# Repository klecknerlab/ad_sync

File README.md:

# ad_sync
Hardware and software design for a USB-based analog/digital synchronizer board.  Developed by the MUVI and Kleckner Labs at UC Merced.

## Description
This project is intended to solve a specific problem: synchronizing a laser scanner and camera setup for 3D volumetric imaging.
To do this, it outputs hardware synchronized digital and analog signals.
The hardware works by converting a single digital bit stream from the on board ESP32 processor to a series of shift registers and a digital-to-analog converter (with ± 10V range).
The update rate is tunable from 30 Hz to 700 kHz, with a ~10 PPM accurate clock (provided by the APLL clock on the ESP32).

The hardware, firmware and software required to run the board is all stored in this repository, with an Apache license.
If you would like to fabricate, modify, or just use these boards, get in touch!

## Features
* 16 synchronized digital outputs.  Four are converted to 5 V and output on external BNC or header pin connections
* 2 synchronized analog outputs, output on BNC or header pins
* 2 auxiliary serial ports (RS-232 levels), tunneled through the main connection, and which can be used to control additional devices
* An RGB output LED, controllable through software, to be used as an indicator light
* A small on-board prototyping area, to add additional functionality
* Pin headers for various on board signals, including unused GPIO ports on the microcontroller.  (These are not usable without a firmware modification.)
* Everything is controlled through a USB port *or* Bluetooth conncection, with simple serial commands.  (To enable bluetooth, use `set_bt_name.py`.)
* In the future, a firmware update may also provide a wifi connection option; the microcontroller is capable of this but the feature has not been coded)

## Project Progress
* [x] Initial board schematics
* [x] Fabricate test hardware
* [x] Feature complete firmware
* [x] USB communications
* [x] Python driver
* [ ] Wifi connection
* [x] Bluetooth connection
* [x] Aux. serial port connections
* [x] Experimental testing and validation
* [x] Synchronizer GUI

## Contents
This project contains four directories:
* `hardware`: the hardware schematics and PCB layout.
* `hardware_fab`: the PCB design output files, which can be sent directly to a board fabricator.
* `firmware`: the Arduino/C++ firmware for the driver board, as a PlatformIO project.  (Note: currently in alpha status.)
* `ad_sync`: a Python library to interface with the board through USB. (Note: currently empty.)

## Python Interface
The device is most easily controlled with the provided Python library.
All of the functions are illustrated in `test.py`, located in this directory.

All of the functions in the communication protocol (described below), also have a corresponding python method with a similar or identical name.

On some OS's you may need to install drivers for the USB chip on the board ([Sillabs CP2104](https://www.silabs.com/developers/usb-to-uart-bridge-vcp-drivers).)

## Description of Synchronized Outputs
The synchronized outputs are fed from an internal memory of up to 16384 samples.
Each sample is a 32 bit unsigned integer.
The high 16 bits are the digital channels, and the low 16 bits are an analog sample.
Typically, the analog sample should contain the full data range (0-65535), and can be dynamically scaled as the signal is generated.
(This way you don't need to upload entirely new data to offset or rescale the analog signal.)

To specify an output, you first upload an arbitrary amount of data (in Python, use the `write_ad` method).
You then tell the device where to read from in memory, by specifying a start address and number of samples (`addr` method).
Additionally, you can specify the output rate in samples/s (`rate` method).

Finally, you can specify that certain digital channels are triggered.
Triggered channels will remain low until a trigger is specified (`trigger` method).
Note that the trigger always starts on the beginning of an output cycle, and can be for one or more cycles.

## Communication Protocol
Although the Python library is convenient, it is also possible to talk to the board directly with serial commands through the USB interface (and eventually: bluetooth and wifi, which will use a serial bridge).

**Command structure:** one to three "words", at most four letters each, followed by 0-3 integers.  Some commands are also followed by arbitrary length binary data.  
All commands are terminated with a linefeed character (`⏎`; this is equivalent to `"\n"` in Python or C).  

The format for binary appended data is `>[number of bytes]>[binary data]`, and should followed by a line feed character.

Note that if the word is longer than 4 letters the extra letters are ignored.
In other words `SYNC AVAIL` is the same as `SYNC AVAI` (or even `SYNC AVAILABLE` if you prefer).  
Lower case letters are converted to upper case internally (i.e. `SynC AvAiXXX` is also equivalent.)

Unless specified otherwise, commands return `ok.⏎` on success.
Error strings will always begin with `ERROR:` and end with `⏎`.

*Note:* For the command words `ANA0`, `ANA1`, `SER1`, and `SER2` there is no space between the letters and number -- this number is part of the command, not an argument!
(If you're wondering why the serial numbering starts with 1: this is because serial 0 is the USB connection.)

### List of Serial Commands
Parameters are specified in square brackets, and correspond to unsigned integers (exception: commands which have an `ON/OFF` option).

**Misc Commands**
* `*IDN⏎`: Returns the identification string for the synchronizer.  (Presently: `USB analog/digital synchronizer (version 1.0)⏎`)
* `LED [r] [g] [b]⏎`: Set the color of the RGB indicator LED.  Each value should be 0-255, and the output is gamma corrected.

**Sync Output Commands**
* `SYNC STAT⏎`: Outputs statistics on the sync DMA buffer output.  Used for debugging, but shouldn't normally be needed.
* `SYNC WRITE [addr] >[n]>[binary data]⏎`: Write synchronous data starting at indicated address (addr < 16384).  
    - Each data point is four bytes, or a uint32.  The highest two bytes are the digital outputs for that sample and the lowest two bytes are the analog signal.  Note that the microcontroller is little-endian, thus the byte order should be `[analog low][analog high][digital low][digital high]`.  
    - The data written should have a length which is a multiple of 4 bytes, but this is not enforced!  (A warning will be issued if this condition is not met.)  There is no padding between samples, and you can upload as many as you want at once.
    - Ideally, the analog data should span the full 0--65535 range.  The amplitude and offset of the output can be controlled with the `ANA[0/1] SCALE` command, so that you don't have to reupload data to rescale the analog output.
* `SYNC [START/STOP]⏎`:
    - Start/stop the synchronous digital outputs by enabling or disabling the shift register outputs and stopping the sync updates.
    - When stopped, the analog channels will default to the values set by `ANA[0/1] SET`.
* `SYNC MODE [analog mode] [digital mode (optional)]⏎`: Set the mode of the sync output.  
	- Analog mode options:
		- `0`: No sync analog output; each channel goes to the default (set w/ `ANA[0/1] SET`)
		- `1`: Analog 0 streams from sync data, analog 1 fixed value (default)
		- `2`: Analog 1 streams from sync data, analog 0 fixed value
		- `3`: Both channels stream, alternating updates.  Even sync data addresses go to analog 0, odd address to analog 1.  Note that this halves the update rate of each channel, relative to the digital signals.
	- Digital mode options:
		- `0`: All 16 outputs derived from sync data (default)
		- `1`: "Or" mode.  Channels 0-7 are logical "or"ed with channels 8-15.  8-15 have the normal output.  (Can be used to superimpose triggered and non-triggered signals.)
        - `2`: "Swap" mode.  Channels 0-7 swapped with 8-15.  (Can be used to switch the
            outputs w/o a reupload.)
        - `3': "Swap-Or" mode.  Apply the swap and then the or operation.
* `SYNC ADDR [addr] [count]⏎`: Change the start address and number of data points for a period of the sync output.
* `SYNC ADDR⏎`: Returns the current sync mode (`SYNC CYCLE [addr] [count]⏎`)
* `SYNC RATE [rate Hz] [rate mHz (optional)]⏎`:
    - Change the synchronous output rate, specified in Hz, with any optional millihertz addition.  (i.e. 100.5 Hz would be specified as `SYNC RATE 100 005⏎` or `SYNC RATE 100 5⏎`.)  Valid values are from 30 to 700000.  
    - Replies with `SYNC RATE = [samples/s] Hz⏎`.  Note that [samples/s] will here be floating point, and reflects the actual frequency as set by the device (will likely be *slightly* different than the requested value)
    - Accuracy/precision is ~10 PPM, as determined by main clock accuracy.
* `ANA[0/1] SCALE [scale] [offset]⏎`:
    - Change the output scale and offset of this channel.  Each scale/offset should be from 0-65536 and covers the range of -10 to 10 V.  
    - `scale` indicates the peak to peak amplitude of the signal (65536 = 20 V peak-to-peak, 3277 = 1.0000 V peak-to-peak)
    - `offset` is the minimum value of the signal (0 = -10 V, 65536 = 10V, 32768 = 0V.)  
    - *Note:* the above scaling assumes the input waveform goes from 0-65535 in the sync data.  If it does not, it will be proportionally smaller.
* `ANA[0/1] SET [value]⏎`:
    - Directly set the analog output value for one of the channels (0=-10V, 65536 = +10V).  No scaling or offset is applied.  
    - *Note 1:* Command ignored if this channel is currently updating synchronously.  
    - *Note 2:* Updating while the sync is running on the other channel will introduce a one sample skip in the output of the synced channel.

**Serial Commands**
* `SER[1/2] WRITE >[n]>[binary data]⏎`: Write `n` bytes to serial port 1/2.  Replies with: `Wrote [n] bytes of data to serial [1/2].⏎`
* `SER[1/2] READ [n (optional)]⏎`:
    - Read at most `n` bytes of data from serial port 1/2  
    - If `n` is not specified (or `n` is greater than the amount of available data), return all available data.  
    - Call is non-blocking: it will not wait for data to be available
    - Reply format is `>[n]>[n bytes of binary]⏎`  
* `SER[1/2] AVAIL⏎`: Return the number of bytes available to be read at that serial port.  Reply format: `[n]⏎`
* `SER[1/2] FLUSH⏎`: Flush the read buffer for a serial port.
* `SER[1/2] RATE [baud rate]⏎`:
    - Set the baud rate for a serial port  
    - The serial format is always 8 bits with a start and stop bit.  (This could be changed by altering the firmware, if needed.)
    - *Note:* Changing the Baud rate of Serial Port 1 will cause an output glitch on the sync outputs.  Unfortunately this is a hardware bug on the microcontroller, which is not correctable!

**Trigger Commands**
* `TRIGER MASK [bit mask]⏎`: A bit mask indicated if each digital output channel is triggered.  Triggered channels output low until triggered.
* `TRIGER [cycles (optional)]⏎`: Activate the trigger for the specified number of cycles.  `cycles=1` is the default.  Note that there may be a delay of up to 256 samples in outputting a triggered signal, due to the output buffering.  Also, triggers always begin at the beginning of a cycle.

**Bluetooth Commands**
* `BLUETOOTH >[n]>[bluetooth name]⏎`:
    - Set the name of the bluetooth device, and enables it
    - Name will be saved to internal flash storage, and will remain after a reboot
    - Name needs to be sent as binary, should be <= 64 bytes (or an error is raised)
    - Replies with `Bluetooth enabled with name: [bluetooth name]⏎`
    - Setting the name to an empty string disables the device (e.g. `BLUETOOTH⏎`)

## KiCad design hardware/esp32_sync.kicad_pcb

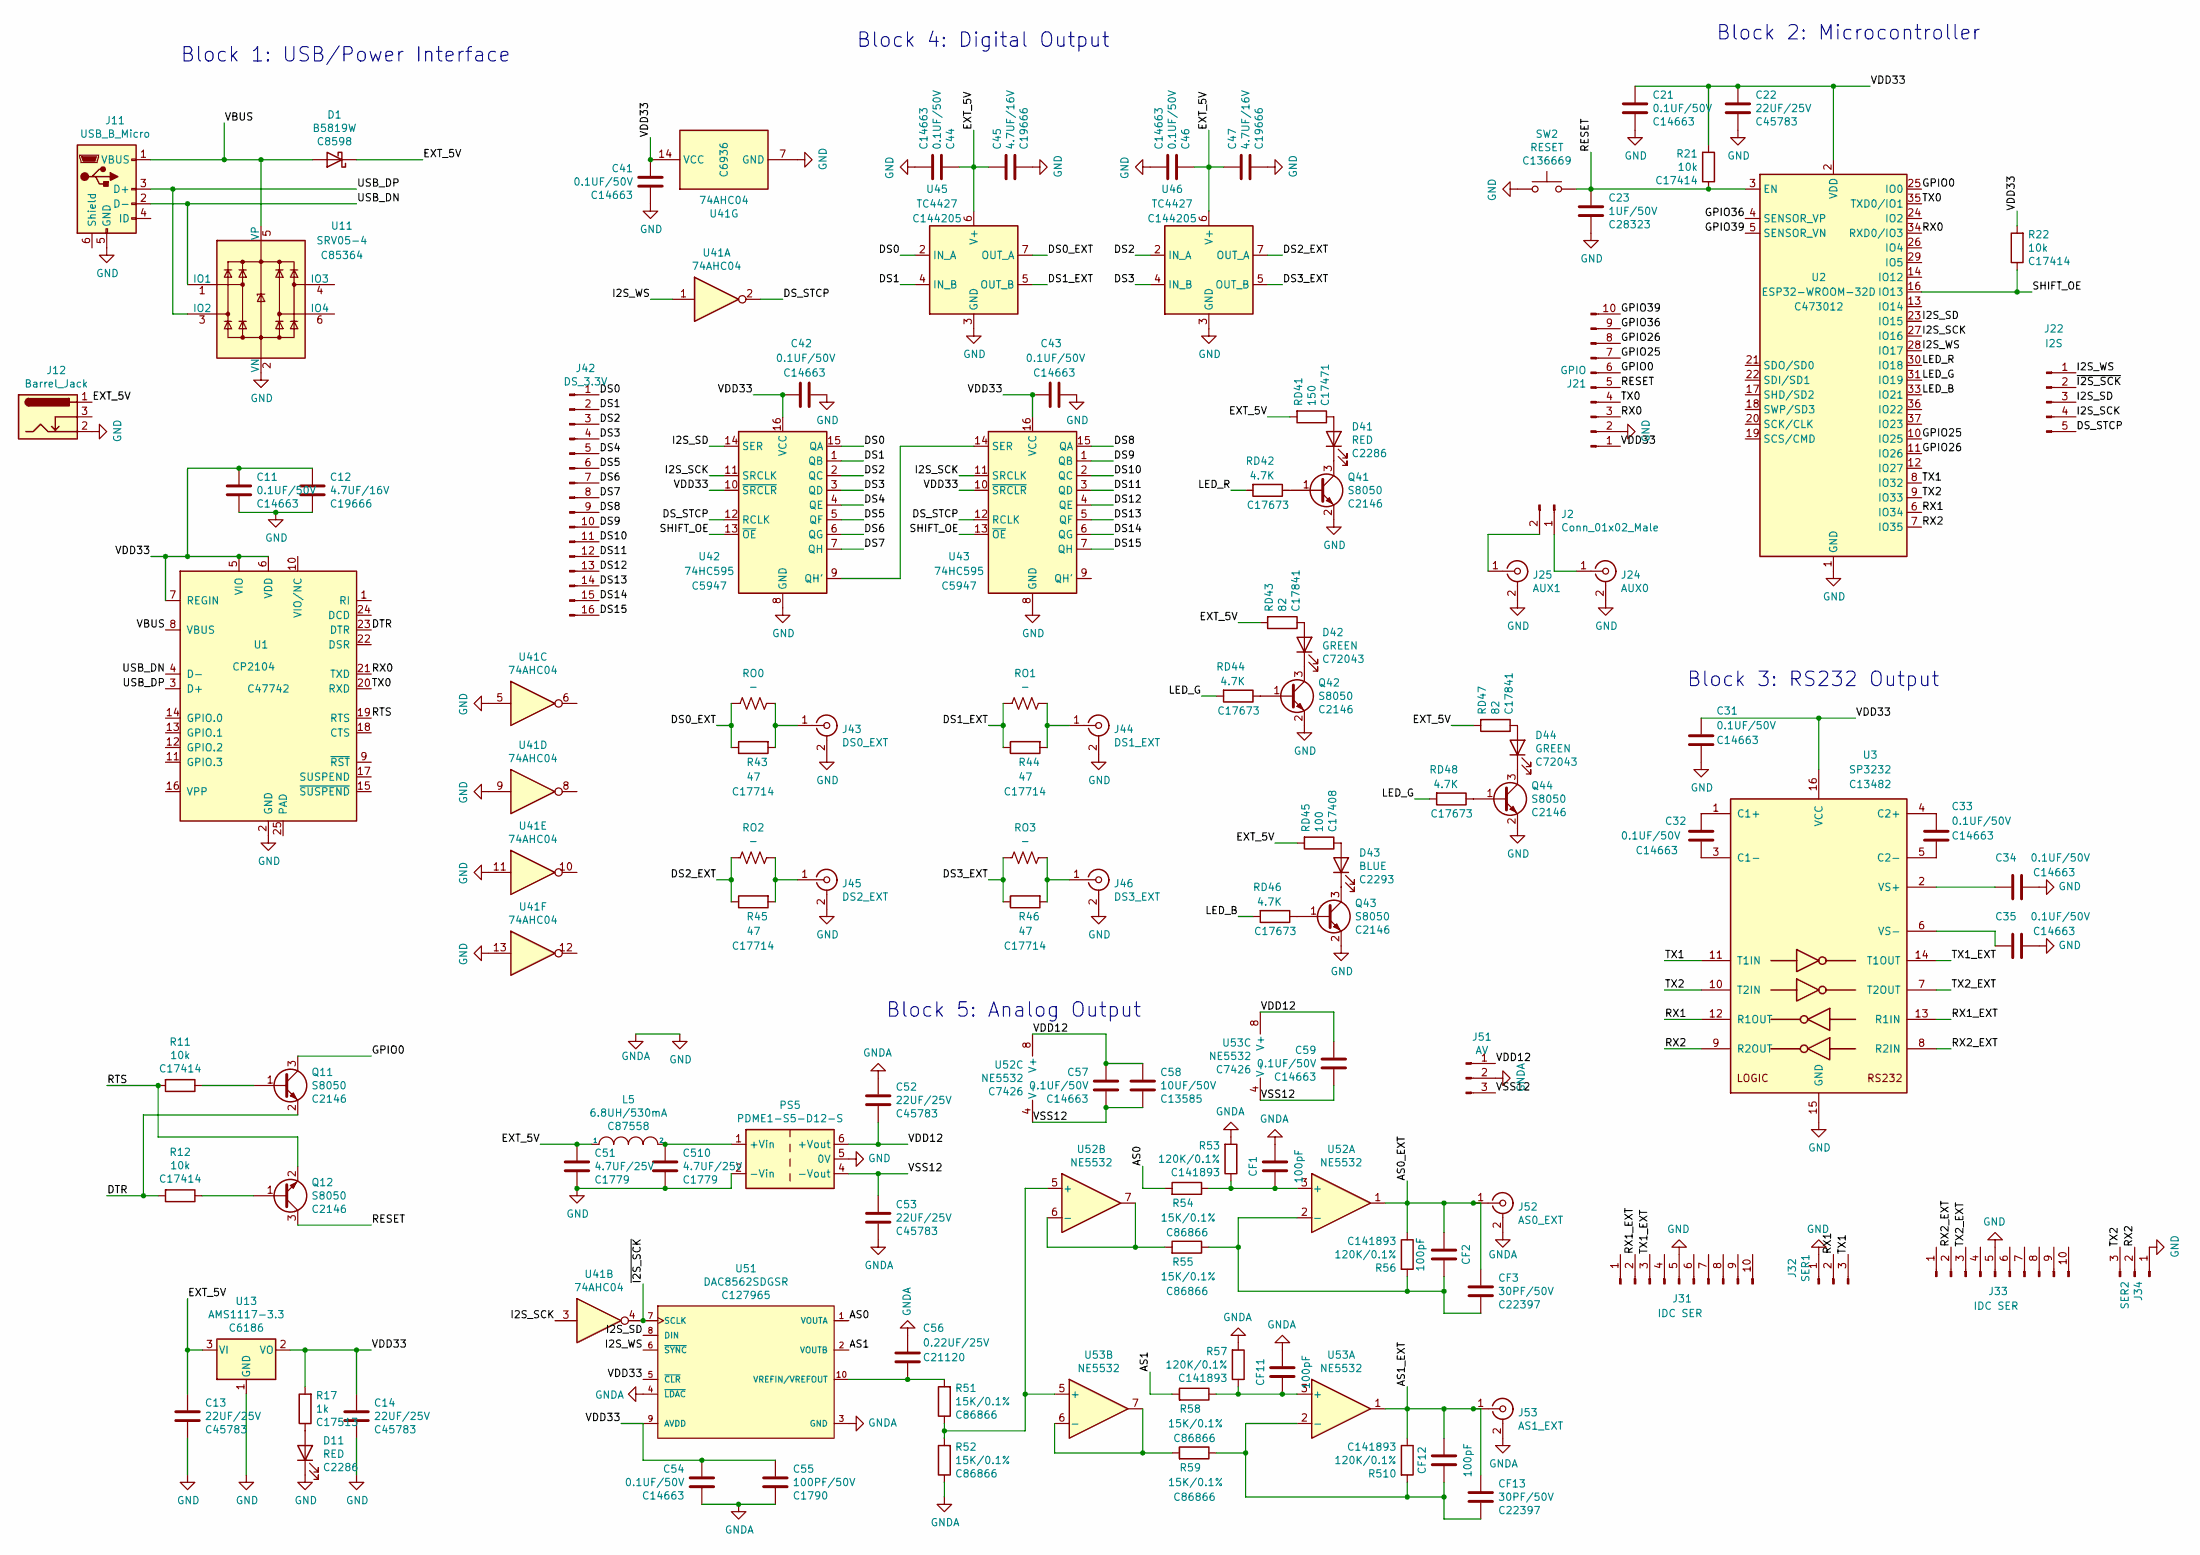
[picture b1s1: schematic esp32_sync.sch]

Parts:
C11, C21, C31, C32, C33, C34, C35, C41, C42, C43, C44, C46, C54, C57, C59: 0.1UF/50V; C_0603_1608Metric; LCSC C14663
C12, C45, C47: 4.7UF/16V; C_0603_1608Metric; LCSC C19666
C13, C14, C22, C52, C53: 22UF/25V; C_0805_2012Metric; LCSC C45783
C23: 1UF/50V; C_0805_2012Metric; LCSC C28323
C51, C510: 4.7UF/25V; C_0805_2012Metric; LCSC C1779
C55: 100PF/50V; C_0805_2012Metric; LCSC C1790
C56: 0.22UF/25V; C_0603_1608Metric; LCSC C21120
C58: 10UF/50V; C_1206_3216Metric; LCSC C13585
CF1, CF2, CF11, CF12: 100pF; C_Axial_L3.8mm_D2.6mm_P7.50mm_Horizontal
CF3, CF13: 30PF/50V; C_0603_1608Metric; LCSC C22397
D1: B5819W; D_SOD-123; LCSC C8598
D11, D41: RED; LED_0603_1608Metric; LCSC C2286
D42, D44: GREEN; LED_0603_1608Metric; LCSC C72043
D43: BLUE; LED_0805_2012Metric; LCSC C2293
J2: Conn_01x02_Male; PinHeader_1x02_P2.54mm_Vertical
J11: USB_B_Micro; USB_Micro-B_Amphenol_10103594-0001LF_Horizontal
J12: Barrel_Jack; BarrelJack_Wuerth_6941xx301002
J21: GPIO; PinHeader_2x05_P2.54mm_Vertical
J22: I2S; PinHeader_1x05_P2.54mm_Vertical
J24: AUX0; BNC_Amphenol_B6252HB-NPP3G-50_Horizontal
J25: AUX1; BNC_Amphenol_B6252HB-NPP3G-50_Horizontal
J31, J33: IDC SER; IDC-Header_2x05_P2.54mm_Vertical
J32: SER1; PinHeader_1x03_P2.54mm_Vertical
J34: SER2; PinHeader_1x03_P2.54mm_Vertical
J42: DS_3.3V; PinHeader_1x16_P2.54mm_Vertical
J43: DS0_EXT; BNC_Amphenol_B6252HB-NPP3G-50_Horizontal
J44: DS1_EXT; BNC_Amphenol_B6252HB-NPP3G-50_Horizontal
J45: DS2_EXT; BNC_Amphenol_B6252HB-NPP3G-50_Horizontal
J46: DS3_EXT; BNC_Amphenol_B6252HB-NPP3G-50_Horizontal
J51: AV; PinHeader_1x03_P2.54mm_Vertical
J52: AS0_EXT; BNC_Amphenol_B6252HB-NPP3G-50_Horizontal
J53: AS1_EXT; BNC_Amphenol_B6252HB-NPP3G-50_Horizontal
L5: 6.8UH/530mA; L_1210_3225Metric; LCSC C87558
PS5: PDME1-S5-D12-S; Converter_DCDC_XP_POWER-IAxxxxS_THT
Q11, Q12, Q41, Q42, Q43, Q44: S8050; SOT-23; LCSC C2146
R11, R12, R21, R22: 10k; R_0805_2012Metric; LCSC C17414
R17: 1k; R_0805_2012Metric; LCSC C17513
R43, R44, R45, R46: 47; R_0805_2012Metric; LCSC C17714
R51, R52, R54, R55, R58, R59: 15K/0.1%; R_0805_2012Metric; LCSC C86866
R53, R56, R57, R510: 120K/0.1%; R_0805_2012Metric; LCSC C141893
RD41: 150; R_0805_2012Metric; LCSC C17471
RD42, RD44, RD46, RD48: 4.7K; R_0805_2012Metric; LCSC C17673
RD43, RD47: 82; R_0805_2012Metric; LCSC C17841
RD45: 100; R_0805_2012Metric; LCSC C17408
RO0, RO1, RO2, RO3: -; R_Axial_DIN0204_L3.6mm_D1.6mm_P7.62mm_Horizontal
SW2: RESET; SW_Push_1P1T_NO_6x6mm_H9.5mm; LCSC C136669
U1: CP2104; QFN-24-1EP_4x4mm_P0.5mm_EP2.6x2.6mm; LCSC C47742
U2: ESP32-WROOM-32D; ESP32-WROOM-32; LCSC C473012
U3: SP3232; HTSSOP-16-1EP_4.4x5mm_P0.65mm_EP3.4x5mm; LCSC C13482
U11: SRV05-4; SOT-23-6; LCSC C85364
U13: AMS1117-3.3; SOT-223; LCSC C6186
U41: 74AHC04; TSSOP-14_4.4x5mm_P0.65mm
U42, U43: 74HC595; SOIC-16_3.9x9.9mm_P1.27mm; LCSC C5947
U45, U46: TC4427; SOIC-8_3.9x4.9mm_P1.27mm; LCSC C144205
U51: DAC8562SDGSR; VSSOP-10_3x3mm_P0.5mm; LCSC C127965
U52: NE5532; SOIC-8_3.9x4.9mm_P1.27mm; LCSC C7426
U53: NE5532; SOIC-8_3.9x4.9mm_P1.27mm

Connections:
/AS0: R54.2, U51.1 (VOUTA)
/AS0_EXT: CF2.1, CF3.1, J52.1 (In), R56.1, U52.1
/AS1: R58.2, U51.2 (VOUTB)
/AS1_EXT: CF12.2, CF13.1, J53.1 (In), R510.1, U53.1
/DS0: J42.1, U42.15 (QA), U45.2 (IN_A)
/DS0_EXT: R43.1, RO0.2, U45.7 (OUT_A)
/DS1: J42.2, U42.1 (QB), U45.4 (IN_B)
/DS1_EXT: R44.1, RO1.2, U45.5 (OUT_B)
/DS2: J42.3, U42.2 (QC), U46.2 (IN_A)
/DS2_EXT: R45.1, RO2.2, U46.7 (OUT_A)
/DS3: J42.4, U42.3 (QD), U46.4 (IN_B)
/DS3_EXT: R46.1, RO3.2, U46.5 (OUT_B)
/DS4: J42.5, U42.4 (QE)
/DS5: J42.6, U42.5 (QF)
/DS6: J42.7, U42.6 (QG)
/DS7: J42.8, U42.7 (QH)
/DS8: J42.9, U43.15 (QA)
/DS9: J42.10, U43.1 (QB)
/DS10: J42.11, U43.2 (QC)
/DS11: J42.12, U43.3 (QD)
/DS12: J42.13, U43.4 (QE)
/DS13: J42.14, U43.5 (QF)
/DS14: J42.15, U43.6 (QG)
/DS15: J42.16, U43.7 (QH)
/DS_STCP: J22.5, U41.2, U42.12 (RCLK), U43.12 (RCLK)
/DTR: Q11.2 (E), R12.2, U1.23 (DTR)
/EXT_5V: C13.1, C44.1, C45.1, C46.1, C47.1, C51.1, D1.1 (K), J12.1, L5.1, RD41.2, RD43.2, RD45.2, RD47.2, U13.3 (VI), U45.6 (V+), U46.6 (V+)
/GPIO0: J21.6, Q11.3 (C), U2.25 (IO0)
/GPIO25: J21.7, U2.10 (IO25)
/GPIO26: J21.8, U2.11 (IO26)
/GPIO36: J21.9, U2.4 (SENSOR_VP)
/GPIO39: J21.10, U2.5 (SENSOR_VN)
/I2S_SCK: J22.4, U2.27 (IO16), U41.3, U42.11 (SRCLK), U43.11 (SRCLK)
/I2S_SD: J22.3, U2.23 (IO15), U42.14 (SER), U51.8 (DIN)
/I2S_WS: J22.1, U2.28 (IO17), U41.1, U51.6 (~SYNC~)
/LED_B: RD46.2, U2.33 (IO21)
/LED_G: RD44.2, RD48.2, U2.31 (IO19)
/LED_R: RD42.2, U2.30 (IO18)
/RESET: C23.1, J21.5, Q12.3 (C), R21.1, SW2.2, U2.3 (EN)
/RTS: Q12.2 (E), R11.2, U1.19 (RTS)
/RX0: J21.3, U1.21 (TXD), U2.34 (RXD0/IO3)
/RX1: J32.2, U2.6 (IO34), U3.12 (R1OUT)
/RX1_EXT: J31.2, U3.13 (R1IN)
/RX2: J34.2, U2.7 (IO35), U3.9 (R2OUT)
/RX2_EXT: J33.2, U3.8 (R2IN)
/SHIFT_OE: R22.1, U2.16 (IO13), U42.13 (~OE), U43.13 (~OE)
/TX0: J21.4, U1.20 (RXD), U2.35 (TXD0/IO1)
/TX1: J32.3, U2.8 (IO32), U3.11 (T1IN)
/TX1_EXT: J31.3, U3.14 (T1OUT)
/TX2: J34.3, U2.9 (IO33), U3.10 (T2IN)
/TX2_EXT: J33.3, U3.7 (T2OUT)
/USB_DN: J11.2 (D-), U1.4 (D-), U11.1 (IO1)
/USB_DP: J11.3 (D+), U1.3 (D+), U11.3 (IO2)
/VBUS: D1.2 (A), J11.1 (VBUS), U1.8 (VBUS), U11.5 (VP)
/VDD12: C52.2, C57.1, C58.1, C59.1, J51.1, PS5.6 (+Vout), U52.8 (V+), U53.8 (V+)
/VDD33: C11.1, C12.1, C14.1, C21.1, C22.1, C31.1, C41.1, C42.2, C43.2, C54.1, C55.1, J21.1, R17.2, R21.2, R22.2, U1.5 (VIO), U1.6 (VDD), U1.7 (REGIN), U2.2 (VDD), U3.16 (VCC), U13.2 (VO), U41.14 (VCC), U42.10 (~SRCLR), U42.16 (VCC), U43.10 (~SRCLR), U43.16 (VCC), U51.5 (~CLR~), U51.9 (AVDD)
/VSS12: C53.1, C57.2, C58.2, C59.2, J51.3, PS5.4 (-Vout), U52.4 (V-), U53.4 (V-)
/~I2S_SCK: J22.2, U41.4, U51.7 (SCLK)
GND: C11.2, C12.2, C13.2, C14.2, C21.2, C22.2, C23.2, C31.2, C34.2, C35.2, C41.2, C42.1, C43.1, C44.2, C45.2, C46.2, C47.2, C51.2, C52.1, C53.2, C54.2, C55.2, C56.1, C510.2, CF1.2, CF11.2, D11.1 (K), J11.5 (GND), J12.2, J21.2, J24.2 (Ext), J25.2 (Ext), J31.5, J32.1, J33.5, J34.1, J43.2 (Ext), J44.2 (Ext), J45.2 (Ext), J46.2 (Ext), J51.2, J52.2 (Ext), J53.2 (Ext), PS5.2 (-Vin), PS5.5 (0V), Q41.2 (E), Q42.2 (E), Q43.2 (E), Q44.2 (E), R52.1, R53.2, R57.2, SW2.1, U1.2 (GND), U2.1 (GND), U2.15 (GND), U2.38 (GND), U2.39 (GND), U3.15 (GND), U11.2 (VN), U13.1 (GND), U41.5, U41.7 (GND), U41.9, U41.11, U41.13, U42.8 (GND), U43.8 (GND), U45.3 (GND), U46.3 (GND), U51.3 (GND), U51.4 (~LDAC~); also elsewhere on the board
unnamed: C32.1, U3.1 (C1+)
unnamed: C32.2, U3.3 (C1-)
unnamed: C33.1, U3.4 (C2+)
unnamed: C33.2, U3.5 (C2-)
unnamed: C34.1, U3.2 (VS+)
unnamed: C35.1, U3.6 (VS-)
unnamed: C56.2, R51.2, U51.10 (VREFIN/VREFOUT)
unnamed: C510.1, L5.2, PS5.1 (+Vin)
unnamed: CF1.1, R53.1, R54.1, U52.3 (+)
unnamed: CF2.2, CF3.2, R55.1, R56.2, U52.2 (-)
unnamed: CF11.1, R57.1, R58.1, U53.3 (+)
unnamed: CF12.1, CF13.2, R59.1, R510.2, U53.2 (-)
unnamed: D11.2 (A), R17.1
unnamed: D41.1 (K), Q41.3 (C)
unnamed: D41.2 (A), RD41.1
unnamed: D42.1 (K), Q42.3 (C)
unnamed: D42.2 (A), RD43.1
unnamed: D43.1 (K), Q43.3 (C)
unnamed: D43.2 (A), RD45.1
unnamed: D44.1 (K), Q44.3 (C)
unnamed: D44.2 (A), RD47.1
unnamed: J2.1, J24.1 (In)
unnamed: J2.2, J25.1 (In)
unnamed: J43.1 (In), R43.2, RO0.1
unnamed: J44.1 (In), R44.2, RO1.1
unnamed: J45.1 (In), R45.2, RO2.1
unnamed: J46.1 (In), R46.2, RO3.1
unnamed: Q11.1 (B), R11.1
unnamed: Q12.1 (B), R12.1
unnamed: Q41.1 (B), RD42.1
unnamed: Q42.1 (B), RD44.1
unnamed: Q43.1 (B), RD46.1
unnamed: Q44.1 (B), RD48.1
unnamed: R51.1, R52.2, U52.5 (+), U53.5 (+)
unnamed: R55.2, U52.6 (-), U52.7
unnamed: R59.2, U53.6 (-), U53.7
unnamed: U42.9 (QH'), U43.14 (SER)

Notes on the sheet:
Block 1: USB/Power Interface
Block 2: Microcontroller
Block 3: RS232 Output
Block 4: Digital Output
Block 5: Analog Output

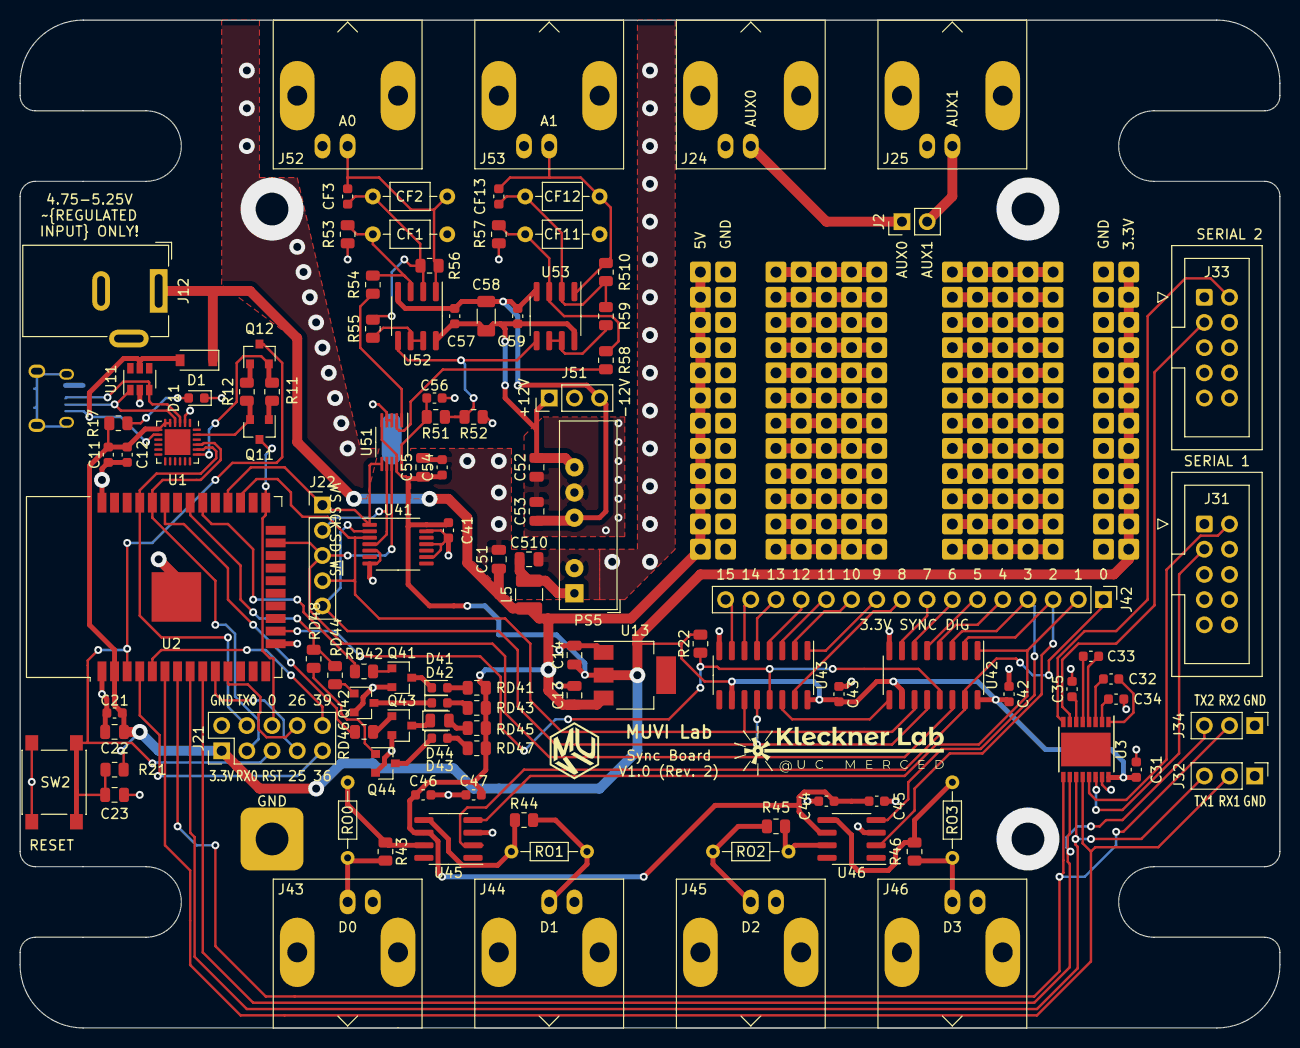
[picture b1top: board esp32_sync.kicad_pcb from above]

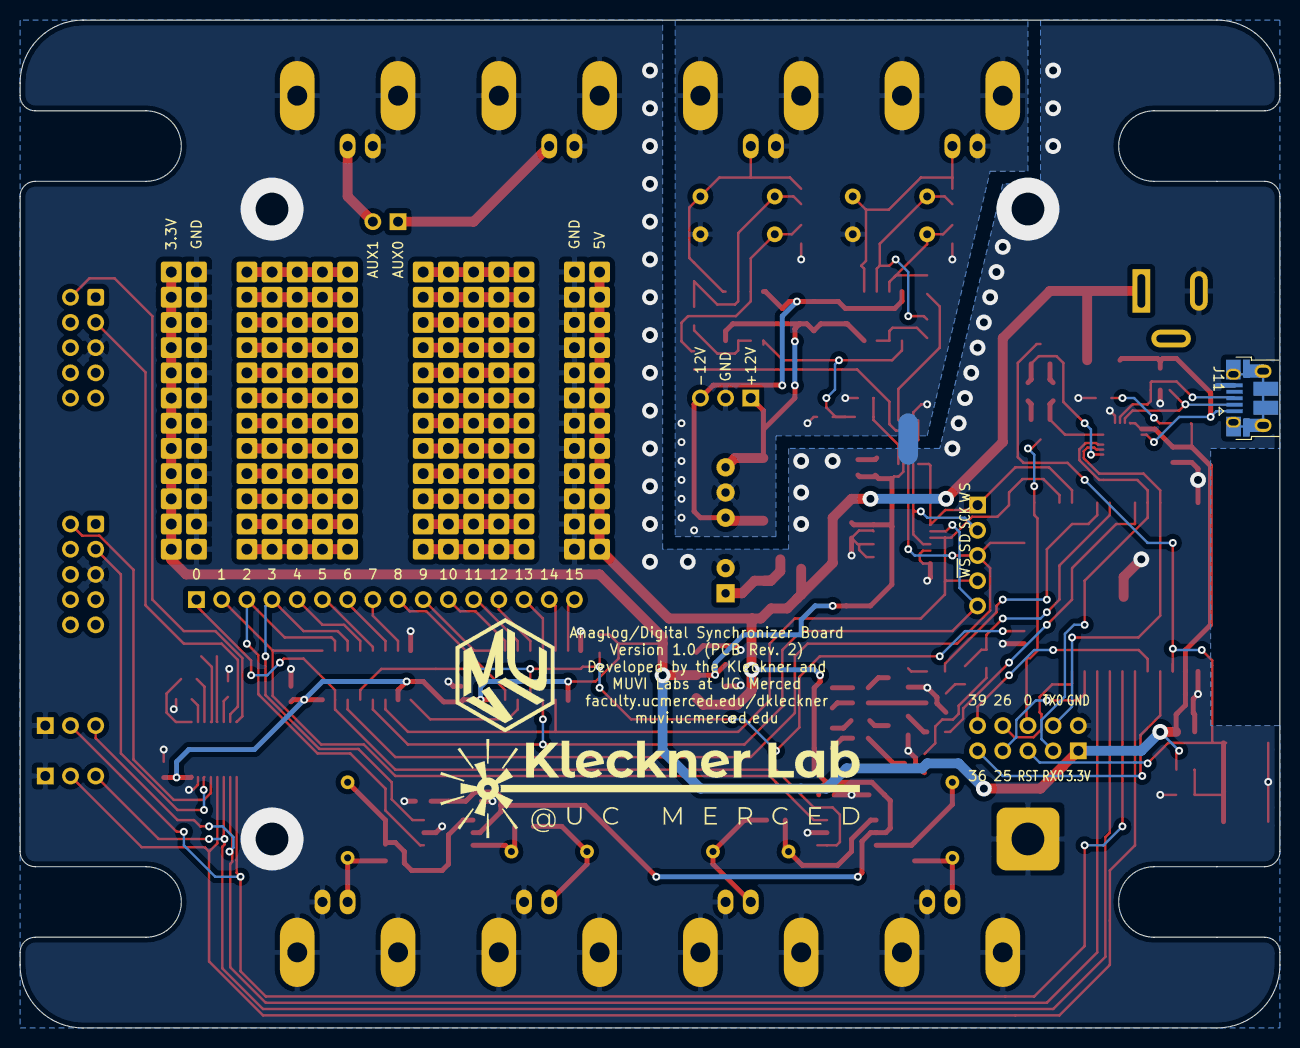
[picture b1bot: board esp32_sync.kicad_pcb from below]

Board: 2 copper layers, 127.0 x 101.6 mm, 117 parts (2 on the bottom side), 96 nets.

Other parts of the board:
GND: SolderWire-0.1sqmm_1x01_D0.4mm_OD1mm
svg2mod: G***; muvi_5mm
svg2mod#2: G***; muvi_10mm
svg2mod#3: G***; muvi

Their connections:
GND: GND.1; also elsewhere on the board

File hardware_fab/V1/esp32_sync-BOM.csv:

Comment,Designator,Footprint,LCSC
0.1UF/50V,"C11,C21,C31,C32,C33,C34,C35,C41,C42,C43,C54,C57,C59,C45A1,C46A1",Capacitor_SMD:C_0603_1608Metric,C14663
4.7UF/16V,"C12,C45B1,C46B1",Capacitor_SMD:C_0603_1608Metric,C19666
22UF/25V,"C13,C14,C22,C52,C53",Capacitor_SMD:C_0805_2012Metric,C45783
1UF/50V,C23,Capacitor_SMD:C_0805_2012Metric,C28323
4.7UF/25V,"C51,C510",Capacitor_SMD:C_0805_2012Metric,C1779
100PF/50V,C55,Capacitor_SMD:C_0805_2012Metric,C1790
0.22UF/25V,C56,Capacitor_SMD:C_0603_1608Metric,C21120
10UF/50V,C58,Capacitor_SMD:C_1206_3216Metric,C13585
100pF,"CF0P1,CF0M1,CF1M1,CF1P1",Capacitor_THT:C_Axial_L3.8mm_D2.6mm_P7.50mm_Horizontal,
B5819W,D1,Diode_SMD:D_SOD-123,C8598
RED,"D11,D41",LED_SMD:LED_0603_1608Metric,C2286
GREEN,D42,LED_SMD:LED_0603_1608Metric,C72043
BLUE,D43,LED_SMD:LED_0805_2012Metric,C2293
USB_B_Micro,J11,Connector_USB:USB_Micro-B_Amphenol_10103594-0001LF_Horizontal,
Barrel_Jack,J12,Connector_BarrelJack:BarrelJack_Wuerth_6941xx301002,
Conn_01x02_Male,J2,Connector_PinHeader_2.54mm:PinHeader_1x02_P2.54mm_Vertical,
GPIO,J21,Connector_PinHeader_2.54mm:PinHeader_2x05_P2.54mm_Vertical,
I2S,J22,Connector_PinHeader_2.54mm:PinHeader_1x04_P2.54mm_Vertical,
AUX0,J24,Connector_Coaxial:BNC_Amphenol_B6252HB-NPP3G-50_Horizontal,
AUX1,J25,Connector_Coaxial:BNC_Amphenol_B6252HB-NPP3G-50_Horizontal,
IDC SER,"J31,J33",Connector_IDC:IDC-Header_2x05_P2.54mm_Vertical,
SER1,J32,Connector_PinHeader_2.54mm:PinHeader_1x03_P2.54mm_Vertical,
SER2,J34,Connector_PinHeader_2.54mm:PinHeader_1x03_P2.54mm_Vertical,
DS_3.3V,J42,Connector_PinHeader_2.54mm:PinHeader_1x16_P2.54mm_Vertical,
DS0_EXT,J43,Connector_Coaxial:BNC_Amphenol_B6252HB-NPP3G-50_Horizontal,
DS1_EXT,J44,Connector_Coaxial:BNC_Amphenol_B6252HB-NPP3G-50_Horizontal,
DS2_EXT,J45,Connector_Coaxial:BNC_Amphenol_B6252HB-NPP3G-50_Horizontal,
DS3_EXT,J46,Connector_Coaxial:BNC_Amphenol_B6252HB-NPP3G-50_Horizontal,
AV,J51,Connector_PinHeader_2.54mm:PinHeader_1x03_P2.54mm_Vertical,
AS0_EXT,J52,Connector_Coaxial:BNC_Amphenol_B6252HB-NPP3G-50_Horizontal,
AS1_EXT,J53,Connector_Coaxial:BNC_Amphenol_B6252HB-NPP3G-50_Horizontal,
6.8UH/530mA,L5,Inductor_SMD:L_1210_3225Metric,C87558
PDME1-S5-D12-S,PS5,Converter_DCDC:Converter_DCDC_XP_POWER-IAxxxxS_THT,
S8050,"Q11,Q12,Q41,Q42,Q43",Package_TO_SOT_SMD:SOT-23,C2146
-,"R0_EXT1,R1_EXT1,R2_EXT1,R3_EXT1",Resistor_THT:R_Axial_DIN0204_L3.6mm_D1.6mm_P7.62mm_Horizontal,
10k,"R11,R12,R21,R22",Resistor_SMD:R_0805_2012Metric,C17414
1k,R17,Resistor_SMD:R_0805_2012Metric,C17513
47,"R43,R44,R45,R46",Resistor_SMD:R_0805_2012Metric,C17714
120K/0.1%,"R53,R56,R57,R510",Resistor_SMD:R_0805_2012Metric,C141893
15K/0.1%,"R51,R52,R54,R55,R58,R59",Resistor_SMD:R_0805_2012Metric,C86866
150,RD41A1,Resistor_SMD:R_0805_2012Metric,C17471
4.7K,"RD41B1,RD42B1,RD43B1",Resistor_SMD:R_0805_2012Metric,C17673
82,RD42A1,Resistor_SMD:R_0805_2012Metric,C17841
100,RD43A1,Resistor_SMD:R_0805_2012Metric,C17408
RESET,SW2,Button_Switch_SMD:SW_Push_1P1T_NO_6x6mm_H9.5mm,C136669
CP2104,U1,Package_DFN_QFN:QFN-24-1EP_4x4mm_P0.5mm_EP2.6x2.6mm,C47742
SRV05-4,U11,Package_TO_SOT_SMD:SOT-23-6,C85364
AMS1117-3.3,U13,Package_TO_SOT_SMD:SOT-223,C6186
ESP32-WROOM-32D,U2,RF_Module:ESP32-WROOM-32,C473012
SP3232,U3,Package_SO:HTSSOP-16-1EP_4.4x5mm_P0.65mm_EP3.4x5mm,C13482
74AHC04,U41,Package_SO:TSSOP-14_4.4x5mm_P0.65mm,C6936
74HC595,"U42,U43",Package_SO:SOIC-16_3.9x9.9mm_P1.27mm,C5947
TC4427,"U45,U46",Package_SO:SOIC-8_3.9x4.9mm_P1.27mm,C144205
DAC8562SDGSR,U51,Package_SO:VSSOP-10_3x3mm_P0.5mm,C127965
NE5532,"U52,U53",Package_SO:SOIC-8_3.9x4.9mm_P1.27mm,C7426

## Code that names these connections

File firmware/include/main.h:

#if !defined(MAIN_H)

#define MAIN_H 1
#include <Arduino.h>


// Is Bluetooth enabled at all?
#define BLUETOOTH_ENABLED 1

// Fast mode.  If enabled output is up to 1050 kHz, but only 8 digital channels.
#define FASTMODE_ENABLED 1

// I2S config options
#include "driver/i2s.h"

#ifdef BLUETOOTH_ENABLED
    #include "BluetoothSerial.h"
    #if !defined(CONFIG_BT_ENABLED) || !defined(CONFIG_BLUEDROID_ENABLED)
        #error Bluetooth is not enabled! Please run `make menuconfig` to and enable it
    #endif
#endif

#ifdef FASTMODE_ENABLED
    #define i2s_buffer_t uint32_t
#else
    #define i2s_buffer_t uint64_t
#endif

// Maximum number of serial characters to process per command queue cycle.
// #define MAX_SERIAL_CHAR_PER_CYCLE   16

// If defined, print debugging messages.  Not recommended for general use!
// #define CMD_DEBUG 1
// #define FREQ_DEBUG 1

// Version numbers.
#define VERSION_MAJOR 1
#define VERSION_MINOR 0


// The output GPIO pin for a variety of functions
#define RX1_PIN         34
#define TX1_PIN         32
#define RX2_PIN         35
#define TX2_PIN         33
#define I2S_CLK_PIN     16
#define I2S_WS_PIN      17
#define I2S_SD_PIN      15
#define OE_PIN          13
#define LED_R_PIN       18
#define LED_G_PIN       19
#define LED_B_PIN       21

const i2s_pin_config_t pin_config = {
    .bck_io_num = I2S_CLK_PIN,
    .ws_io_num = I2S_WS_PIN,
    .data_out_num = I2S_SD_PIN,
    .data_in_num = -1,
};

// LED output gamma -- here matched to typical displays
#define LED_GAMMA       2.2

// The trim is used to scale each output so that max brightness = white
// Output duty cycle is proportional to trim; 65536 is maximum!
// Testing found that with no trim, led 225 255 180 gave white
// R_TRIM = (255/255)^2.2 * 65536
#define LED_R_TRIM      65536
// G_TRIM = (255/255)^2.2 * 65536
#define LED_G_TRIM      65536
// B_TRIM = (180/255)^2.2 * 65536
#define LED_B_TRIM      30457
const uint32_t LED_TRIM[3] = {LED_R_TRIM, LED_G_TRIM, LED_B_TRIM};
const uint8_t LED_PINS[3] = {LED_R_PIN, LED_G_PIN, LED_B_PIN};

// LED outputs a nice sequence of colors on boot, as defined here
#define LED_STARTUP_LEN 5
// Interval is in ms
#define LED_STARTUP_INTERVAL 750
const uint8_t LED_STARTUP_SEQ[LED_STARTUP_LEN][3] = {
    {  0,   0,   0},
    {  0,   0, 255},
    {  0, 255, 255},
    {225, 255, 255},
    {  0,   0,   0},
};
extern int startup_colors_active;

// The size of various buffers.
#define SER_BUFFER_SIZE 1024 // Used to buffer all inputs/outputs -- this is in addition to the built in serial buffer, which is 64 bytes.
#define SYNC_DATA_SIZE  16384 // Sync data storage.  Larger sizes seem to result in memory errors.
#define I2S_WRITE_BUFFER_SIZE 64 // Used to compute output values


// General purpose macros
#define min(a,b) (((a)<(b))?(a):(b))
#define max(a,b) (((a)>(b))?(a):(b))

// Bit depth of I2S output
// Note: if you need to change this, it will require *many* alterations to other parts of the code!
// (This is just defined for convenience -- don't change it!)
#define I2S_BIT_DEPTH 24

// Globally shared variables and arrays
// Most of these are output settings which need to be modified by the command queue

// LED look up table; used for gamma correction
extern uint16_t LED_LUT[256];

void set_led_color(int r, int g, int b);

// I2S buffer used to write new samples
// extern uint64_t i2s_write_buffer[I2S_WRITE_BUFFER_SIZE]; // Does not need to be global

// Data for the sync outputs
extern uint32_t sync_data[SYNC_DATA_SIZE];

// The start and length of the current cycle
extern int sync_start, sync_cycles;

// Is the sync output active?
extern int sync_active;

// Minimum and maximum frequency, set by the limits of the APLL clock
// Also depends on fast mode (32 clock ticks per update) vs regular mode (48)
#ifdef FASTMODE_ENABLED
    #define MIN_FREQ 45
    #define MAX_FREQ 1050000
#else
    #define MIN_FREQ 30
    #define MAX_FREQ 700000
#endif

// Used to compute "sync stat" output
extern uint last_bytes_written, cycles_since_write;
extern unsigned long buffer_update_time, last_sync_update;

// Analog default outputs when not in sync mode
extern uint16_t ana0_set, ana1_set;

// Analog channel flags; bit 0 => ana0, bit 1 -> ana1
// If update is set for a channel, then the "default" value needs to be sent to the DAC
extern int analog_update, analog_sync_mode;

// Used to scale analog output
extern uint32_t ana0_multiplier, ana0_offset, ana1_multiplier, ana1_offset;

// Digital output mode
extern int digital_sync_mode;

// Trigger count
extern int trigger_count;
extern uint32_t trigger_mask;

// Function to change frequency
float sync_freq(float freq);

// Maximum string length for bluetooth serial, to avoid infinite writes
#ifdef BLUETOOTH_ENABLED
    #define SERIAL_BT_MAX_WRITE 1024
    #define BT_NAME_MAX_LENGTH 256
    extern char bt_name[BT_NAME_MAX_LENGTH+1];
#endif
esp_err_t bluetooth_set_name(const char* name);

// Circular buffer class
// This is a non-blocking way of storing serial input/output.
// It will fail silently on overlow, but set the overflow variable.
// Code in "circular_buffer.cpp"
class CircularBuffer {
    public:
        uint8_t buffer[SER_BUFFER_SIZE];
        uint8_t *b_current, *b_end;
        int start, available, overflow;

        CircularBuffer();
        int write(const uint8_t *s);
        int write(const char *s);
        int write(const uint8_t *s, int nbytes);
        int write(const char *s, int nbytes);
        int write(const uint8_t c);
        int from_stream(Stream &stream);
        int to_stream(HardwareSerial &stream);
        #ifdef BLUETOOTH_ENABLED
            int to_stream(BluetoothSerial &stream);
        #endif
        int to_stream(CircularBuffer &buf);
        uint8_t * get_buffer(int * max_data);
        void flush();
};

extern CircularBuffer ser0_output, ser1_input, ser1_output, ser2_input, ser2_output;

#ifdef BLUETOOTH_ENABLED
    extern CircularBuffer serbt_output;
#endif

#endif

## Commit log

2021-01-05 Initial commit. (Hardware complete, firmware partial, python library missing.)
2021-01-05 Added board image.
2021-01-05 Removed DS_Store files from repo.
2021-01-07 Mostly complete firmware.
2021-01-07 Preliminary version of python library, updated firmware.
2021-01-10 Complete python library and firmware!
2021-01-10 README update.
2021-01-11 Added bluetooth functionality; currently buggy!
2021-01-12 Serial buffer rewrite, fixed serial baud change problem (hardware bug!)
2021-01-12 Code cleanup, added startup LED sequence
2021-01-15 Modified firmware for hardware, rev. 2 of PCB.
2021-01-26 Added top plate drawing, minor fixes
2021-01-27 Added GUI (muvi_sync script)
2021-01-28 Addded galvo delay compensation
2021-01-29 GUI improvements.
2021-01-29 Added swap mode to firmware, updated GUI
2021-01-29 Added LED control, reenabled bluetooth
2021-02-11 Implemented two color mode.
2021-02-18 Partially finished fast_output mode.
2021-02-18 Two color in main branch.
2021-02-24 Added new options to muvi_sync: double pulse, triggered start, cont. frames.
2021-03-04 Serial added to GUI
2021-03-04 Minor tweaks to serial GUI
